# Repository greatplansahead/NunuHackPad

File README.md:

# MyHackPad

I tried making a macropad. it was my first time making a PCB, designing a case and writing firmware! The pcb looks nice and the case works however, i had some trouble with the firmware. the kmk hopefully works but qmk could not pass the lint check.

it is a 3x3 macropad with an encoder and 4 neopixels
BOM:
- 8x MX-Style switches
- 8x Through-hole 1N4148 Diodes
- 8x Blank DSA keycaps(any color)
- 1x EC11 Rotary encode
- 4x SK6812 MINI-E LEDs
- 4x M3x16mm screws
- 4x M3 hex nuts
- 3D printed case(any color)

here are some pictures!

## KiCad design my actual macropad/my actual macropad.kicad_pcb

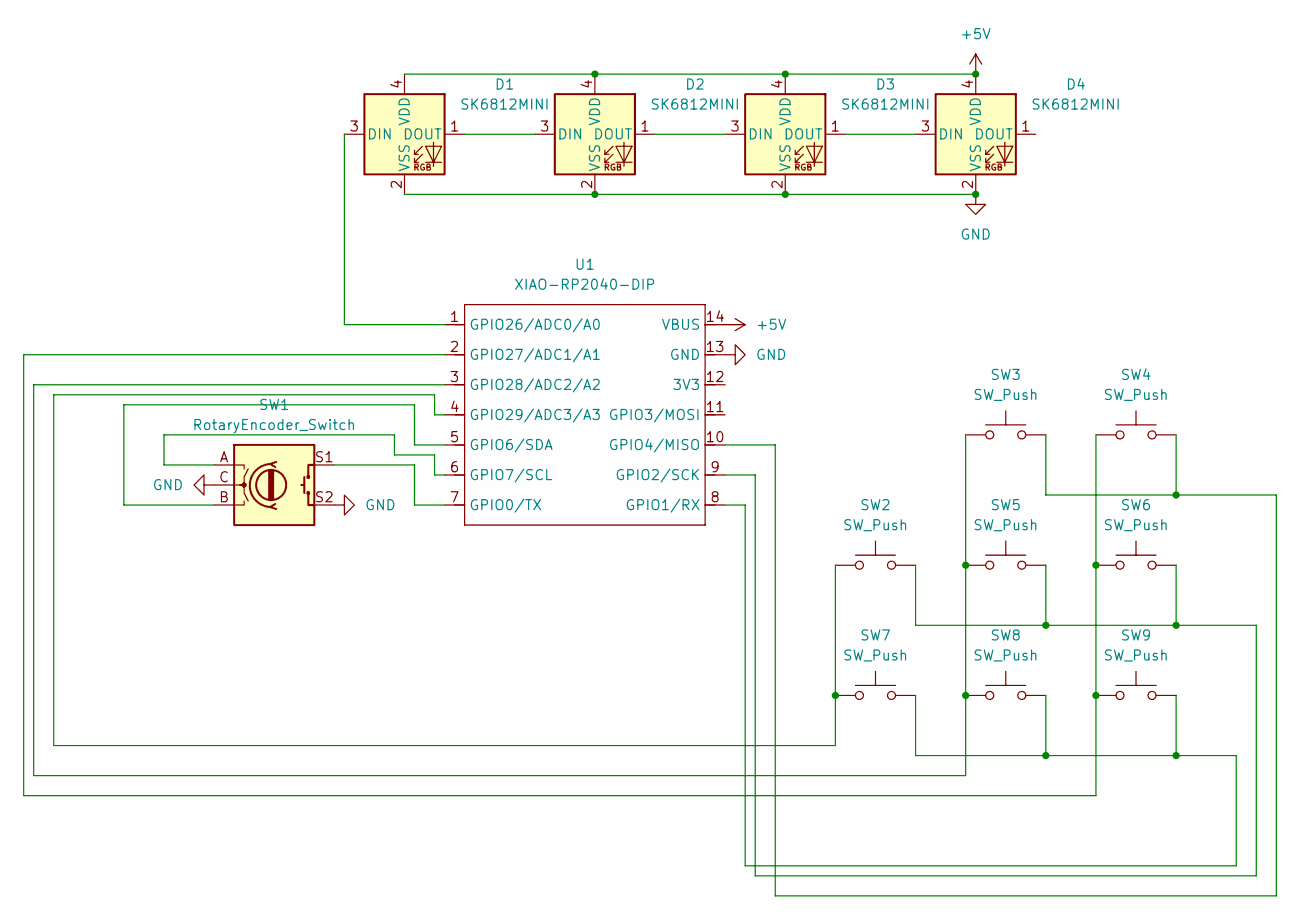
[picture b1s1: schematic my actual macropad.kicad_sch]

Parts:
D1, D2, D3, D4: SK6812MINI; LED_SK6812MINI_PLCC4_3.5x3.5mm_P1.75mm
SW1: RotaryEncoder_Switch; RotaryEncoder_Alps_EC11E-Switch_Vertical_H20mm
SW2, SW3, SW4, SW5, SW6, SW7, SW8, SW9: SW_Push; SW_Cherry_MX_1.00u_PCB
U1: XIAO-RP2040-DIP

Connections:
+5V: D1.4 (VDD), D2.4 (VDD), D3.4 (VDD), D4.4 (VDD), U1.14 (VBUS)
GND: D1.2 (VSS), D2.2 (VSS), D3.2 (VSS), D4.2 (VSS), SW1.C, SW1.S2, U1.13 (GND)
unnamed: D1.3 (DIN), U1.1 (GPIO26/ADC0/A0)
unnamed: D1.1 (DOUT), D2.3 (DIN)
unnamed: D2.1 (DOUT), D3.3 (DIN)
unnamed: D3.1 (DOUT), D4.3 (DIN)
unnamed: SW1.S1, U1.7 (GPIO0/TX)
unnamed: SW7.2, SW8.2, SW9.2, U1.8 (GPIO1/RX)
unnamed: SW2.2, SW5.2, SW6.2, U1.9 (GPIO2/SCK)
unnamed: SW3.2, SW4.2, U1.10 (GPIO4/MISO)
unnamed: SW1.B, U1.5 (GPIO6/SDA)
unnamed: SW1.A, U1.6 (GPIO7/SCL)
unnamed: SW4.1, SW6.1, SW9.1, U1.2 (GPIO27/ADC1/A1)
unnamed: SW3.1, SW5.1, SW8.1, U1.3 (GPIO28/ADC2/A2)
unnamed: SW2.1, SW7.1, U1.4 (GPIO29/ADC3/A3)

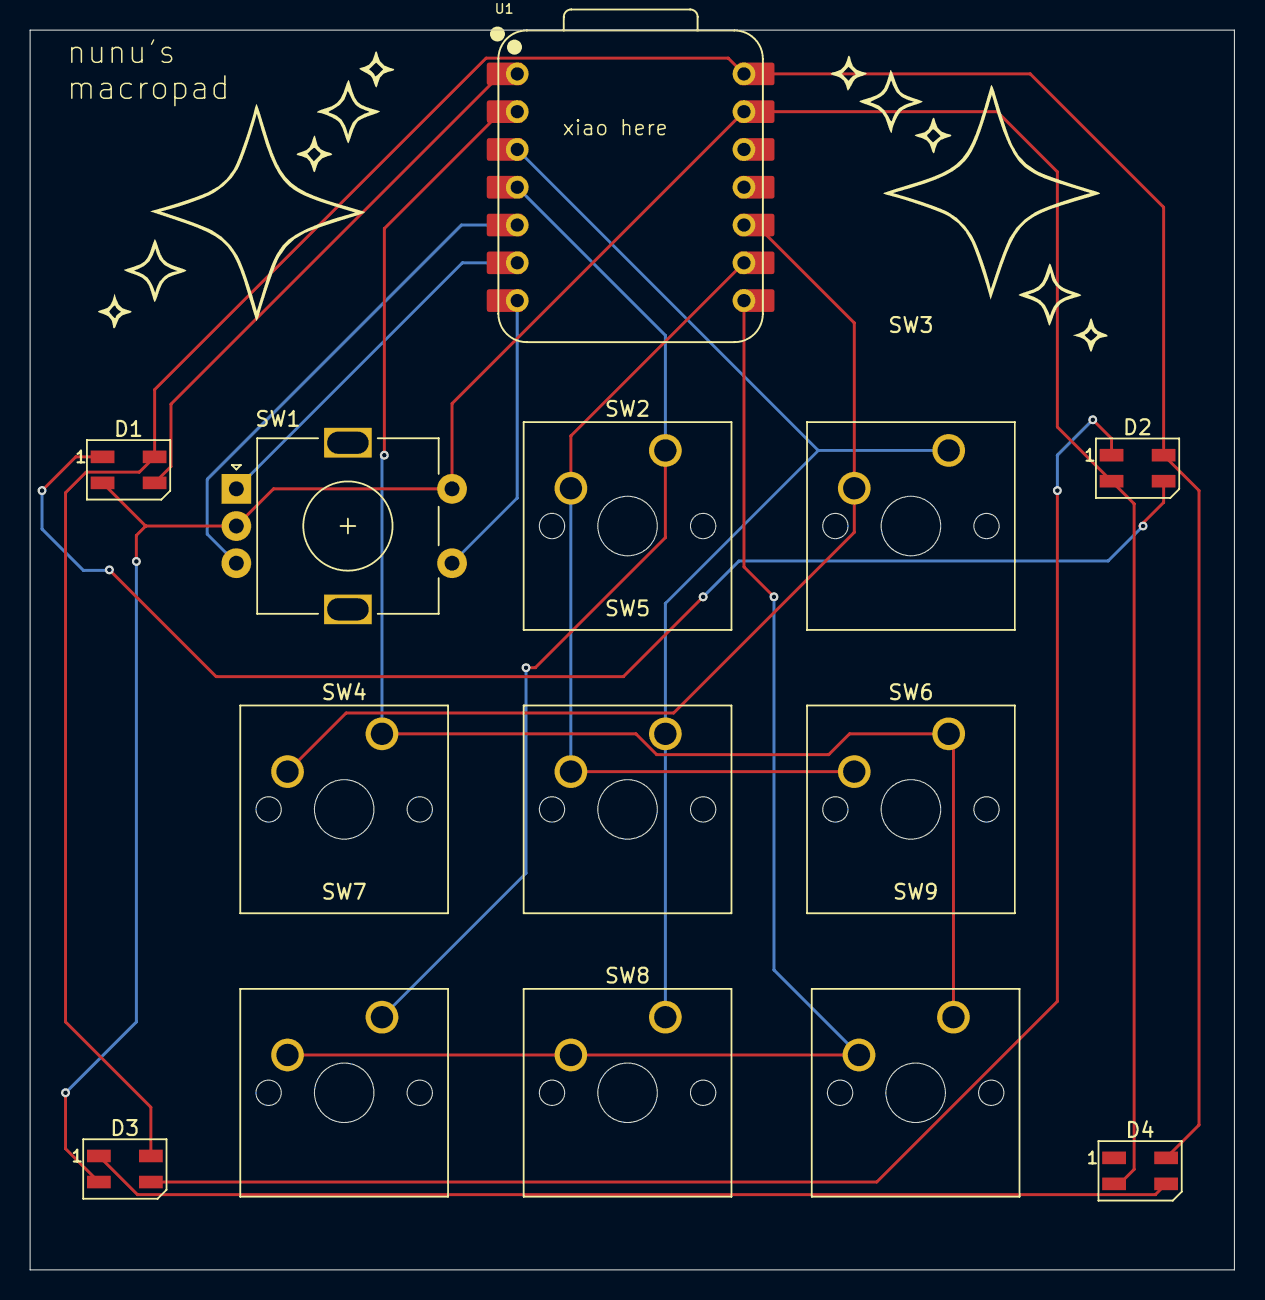
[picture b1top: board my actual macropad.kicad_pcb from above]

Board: 2 copper layers, 81.0 x 83.3 mm, 14 parts (0 on the bottom side), 15 nets.

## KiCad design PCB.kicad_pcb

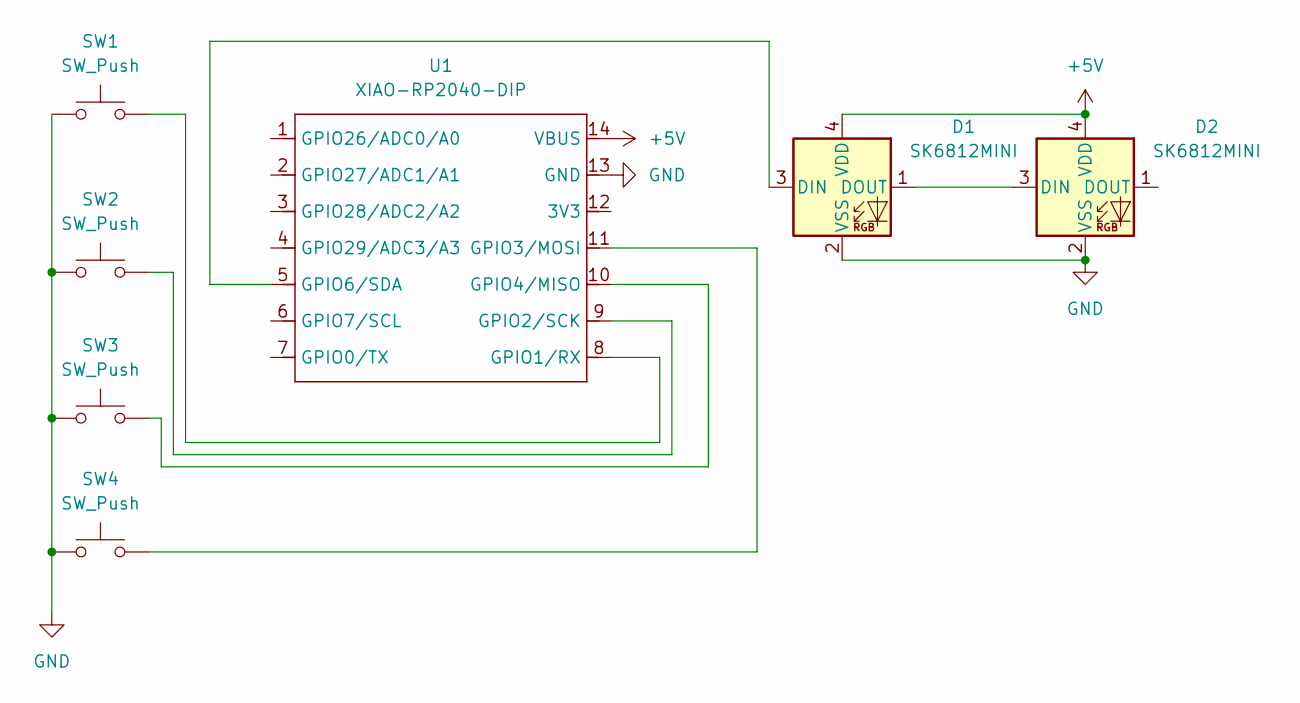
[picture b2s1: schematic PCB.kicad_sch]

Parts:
D1, D2: SK6812MINI; LED_SK6812MINI_PLCC4_3.5x3.5mm_P1.75mm
SW1, SW2, SW3, SW4: SW_Push; SW_Cherry_MX_1.00u_PCB
U1: XIAO-RP2040-DIP

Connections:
+5V: D1.4 (VDD), D2.4 (VDD), U1.14 (VBUS)
GND: D1.2 (VSS), D2.2 (VSS), SW1.1, SW2.1, SW3.1, SW4.1, U1.13 (GND)
unnamed: D1.3 (DIN), U1.5 (GPIO6/SDA)
unnamed: D1.1 (DOUT), D2.3 (DIN)
unnamed: SW1.2, U1.8 (GPIO1/RX)
unnamed: SW2.2, U1.9 (GPIO2/SCK)
unnamed: SW4.2, U1.11 (GPIO3/MOSI)
unnamed: SW3.2, U1.10 (GPIO4/MISO)

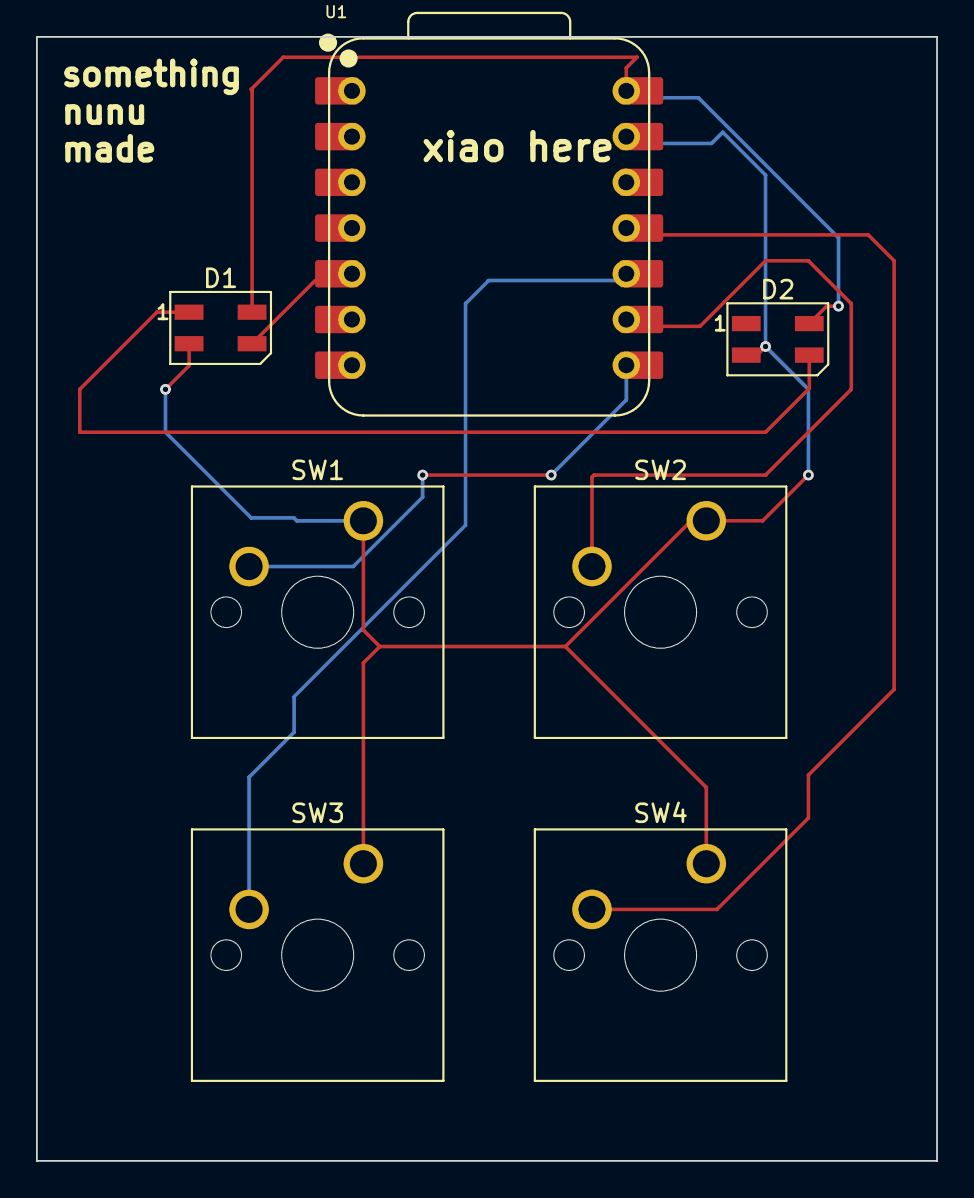
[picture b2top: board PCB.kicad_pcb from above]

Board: 2 copper layers, 50.0 x 62.4 mm, 7 parts (0 on the bottom side), 8 nets.

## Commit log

2024-09-13 KiCad project created
    I made this?
2024-09-13 Add submodules
2024-09-13 add footprint libraries
2024-09-13 Finished Part 3 of the Guide
2024-09-13 Update README.md
    Ideation
2024-09-20 Started making my switches and got the right mcu symbol
    Ummmm.... alot has happened. Finally got the right MCU symbol for the schematic and decided to move ahead and start laying the switches down. Still deciding on what I want. The rotartty encoder with 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
    Clearly I need to get this show on the read with only 11 days left to finish it. Lets GOOOOOOOOOOOO
2024-10-20 New changes
    alot and not much has happened
2024-10-25 Assigning footprints
    tried to finish this before the end but couldn't :(. I couldn't find the rp2040 with holes footprint.
    I will still continue designing the other parts.
2025-02-15 update to pcb and schematic
    made with following the guide. will change to make my own
2025-02-19 new macropad pcb
2025-02-21 organisation
